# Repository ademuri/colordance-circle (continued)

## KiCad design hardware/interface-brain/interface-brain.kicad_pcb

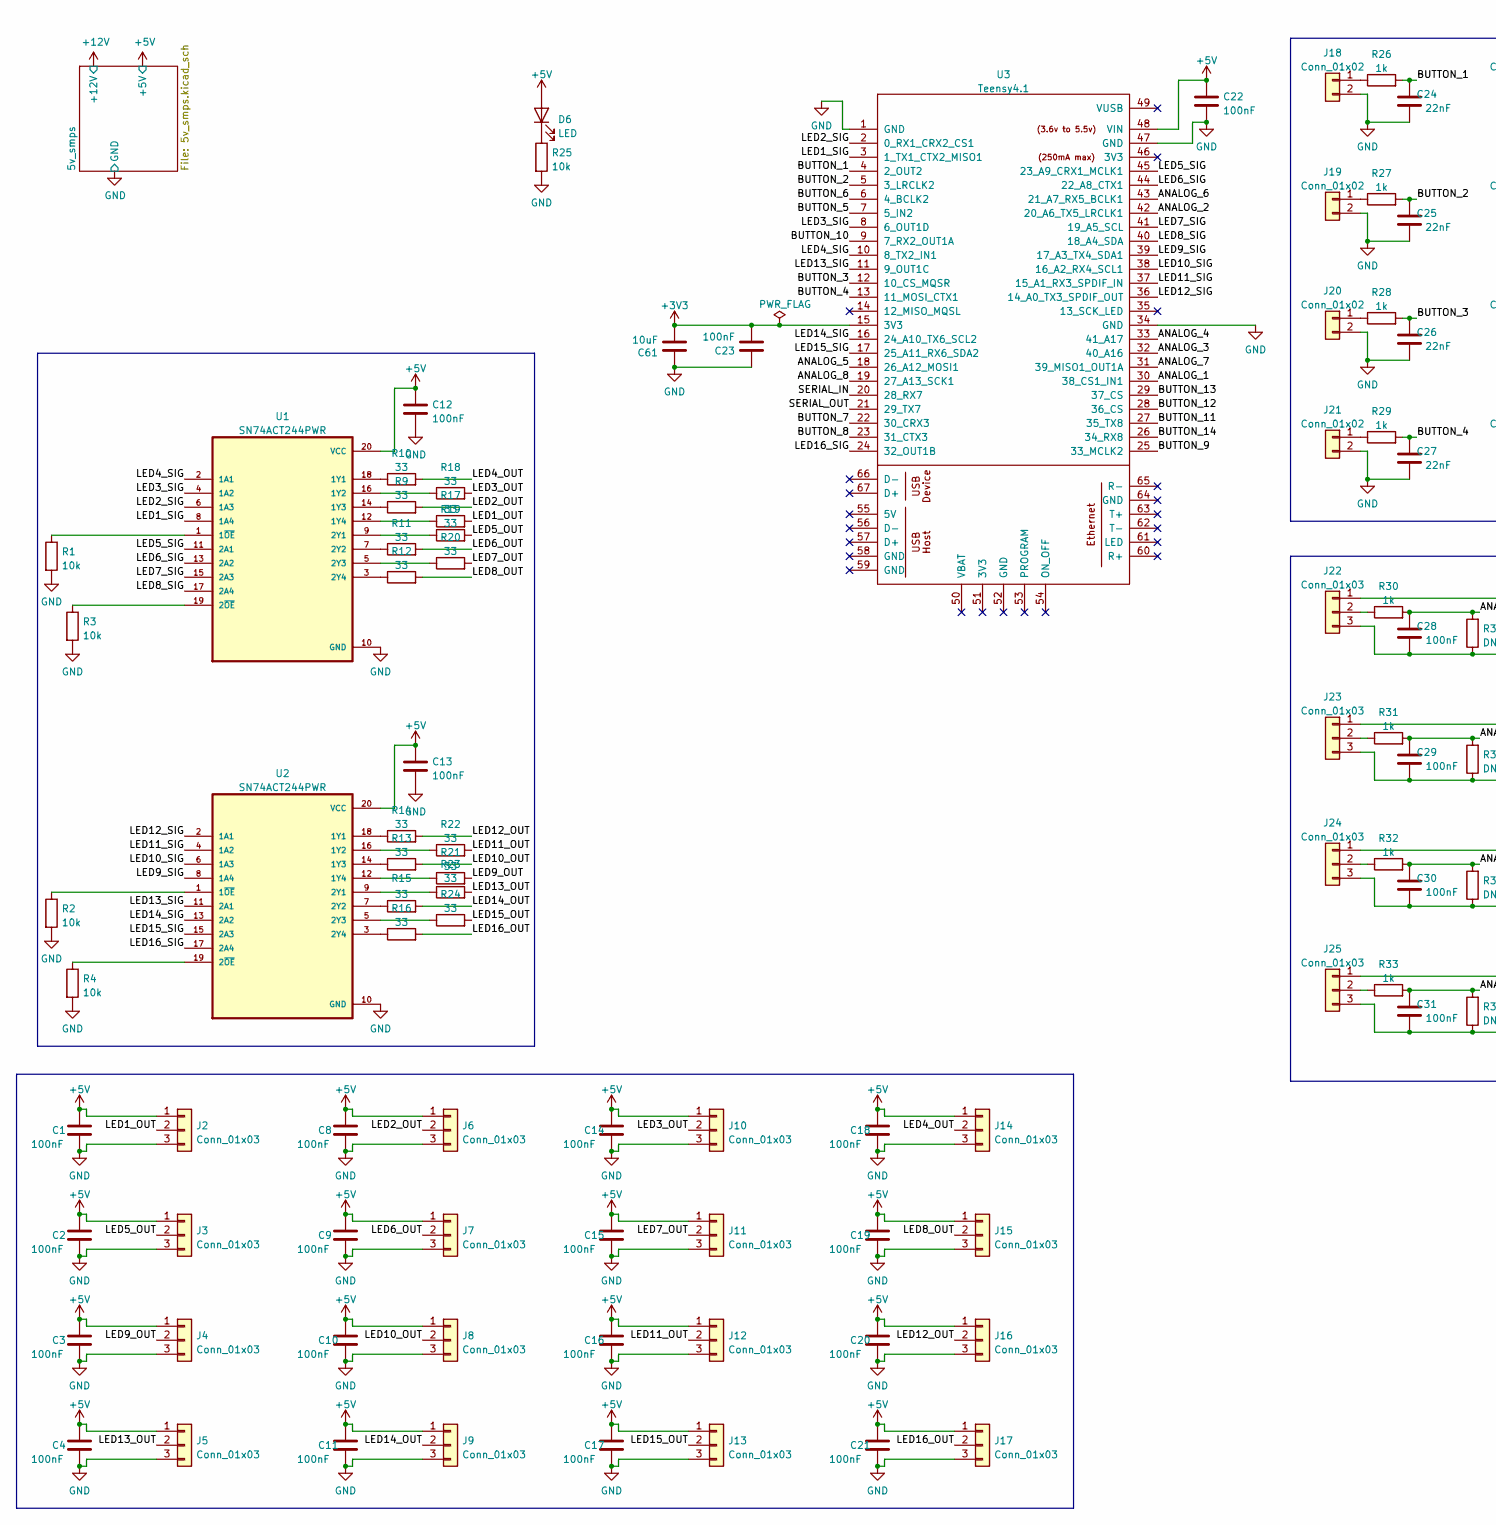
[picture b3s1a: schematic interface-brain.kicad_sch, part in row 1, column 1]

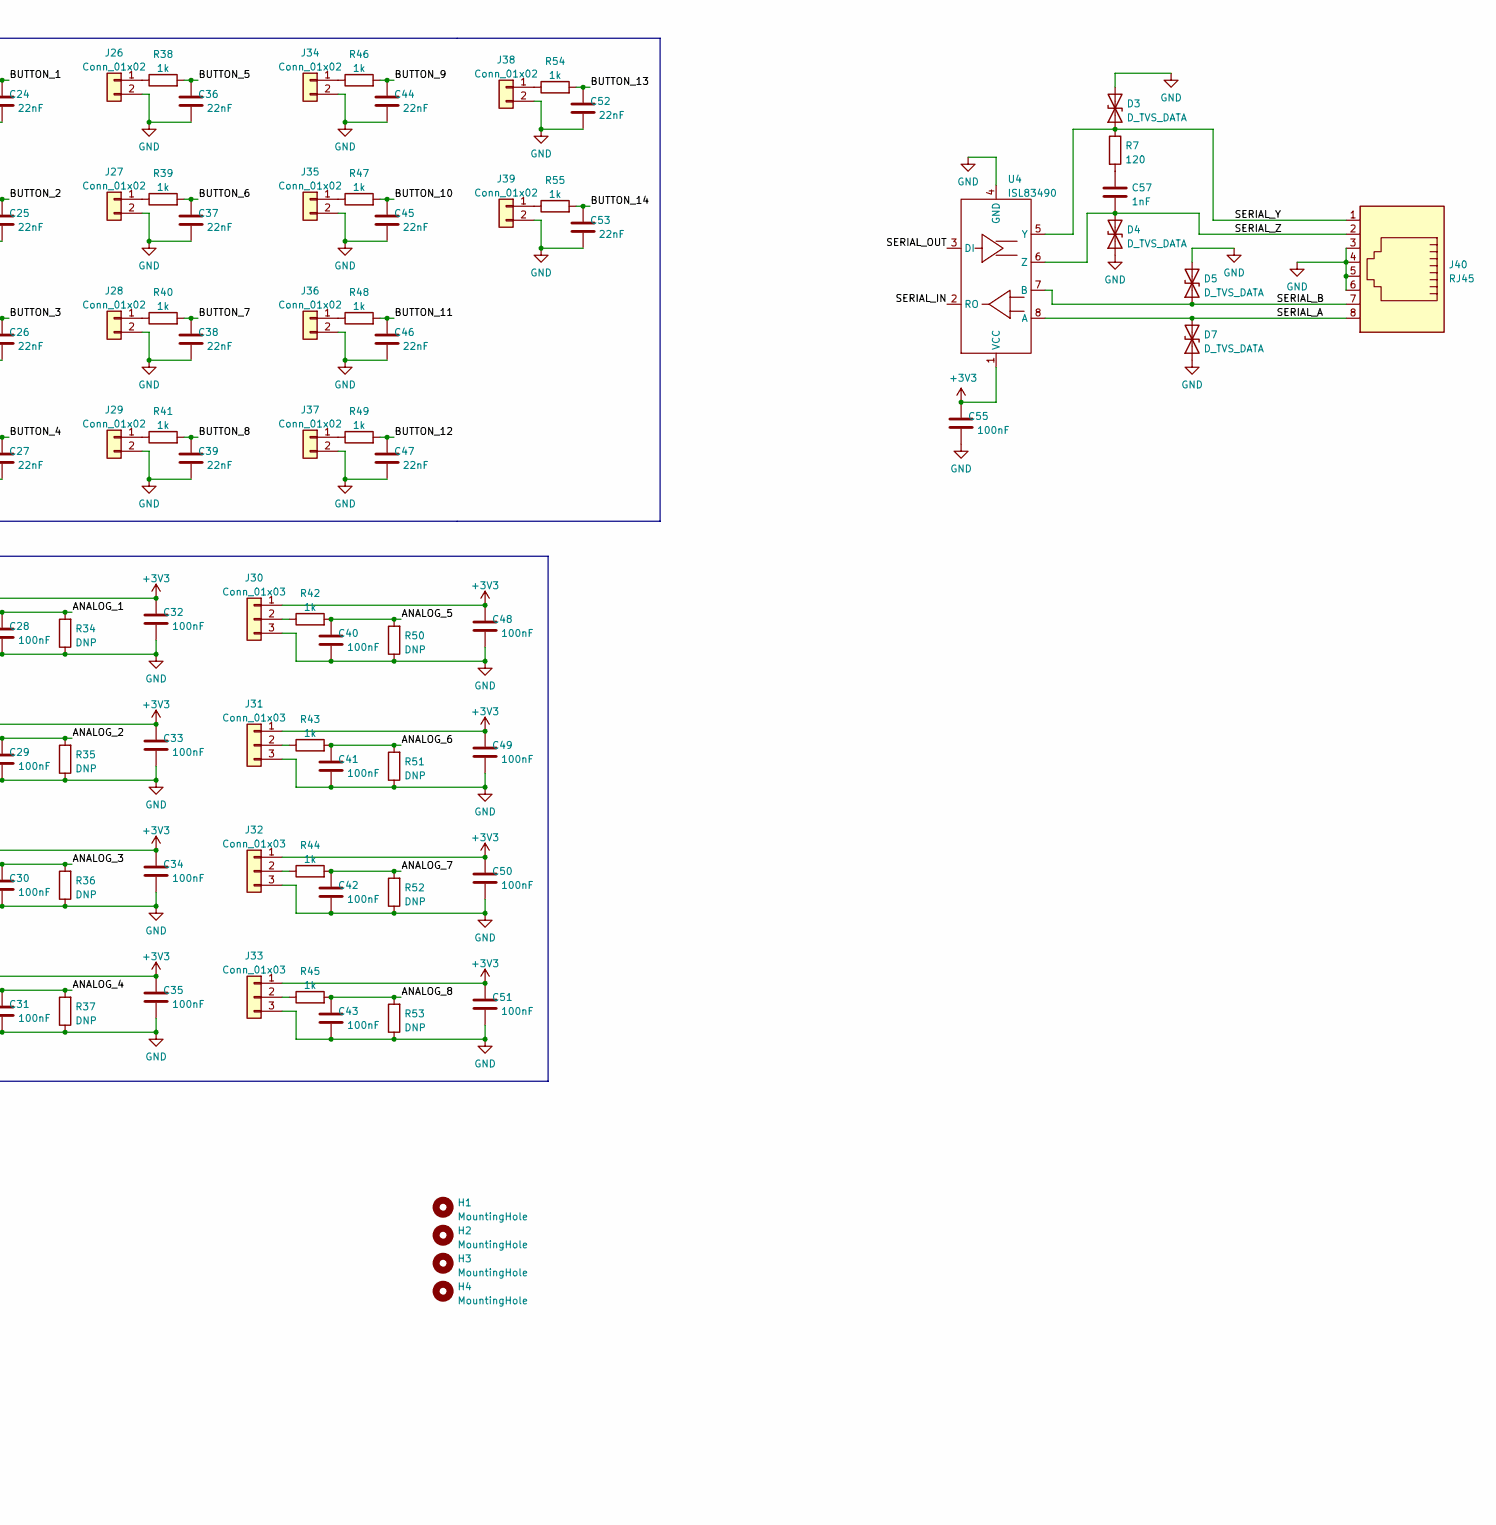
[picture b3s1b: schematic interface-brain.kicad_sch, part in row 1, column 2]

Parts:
C1, C2, C3, C4, C8, C9, C10, C11, C12, C13, C14, C15, C16, C17, C18, C19, C20, C21, C22, C23, C28, C29, C30, C31, C32, C33, C34, C35, C40, C41, C42, C43, C48, C49, C50, C51, C55: 100nF; C_0402_1005Metric; LCSC C307331
C24, C25, C26, C27, C36, C37, C38, C39, C44, C45, C46, C47, C52, C53: 22nF; C_0402_1005Metric; LCSC C1532
C57: 1nF; C_0402_1005Metric; LCSC C1523
C61: 10uF; C_0805_2012Metric; LCSC C15850
D3, D4, D5, D7: D_TVS_DATA; D_SMB; MPN SMBJ6.0CD-M3/H
D6: LED; LED_0603_1608Metric; LCSC C2286
H1, H2, H3, H4: MountingHole; MountingHole_3.2mm_M3
J2, J3, J4, J5, J6, J7, J8, J9, J10, J11, J12, J13, J14, J15, J16, J17, J22, J23, J24, J25, J30, J31, J32, J33: Conn_01x03; MiniPV_69167-X03XXX_1x03_P2.54mm_Polarized_Vertical; MPN 69167-103HLF
J18, J19, J20, J21, J26, J27, J28, J29, J34, J35, J36, J37, J38, J39: Conn_01x02; MiniPV_76384-X02XX_1x02_P2.54mm_Vertical; MPN 76384-302LF
J40: RJ45; RJ45_Amphenol_54602-x08_Horizontal; MPN 54601-908WPLF
R1, R2, R3, R4, R25: 10k; R_0603_1608Metric; LCSC C25804
R7: 120; R_0603_1608Metric; LCSC C22787
R9, R10, R11, R12, R13, R14, R15, R16, R17, R18, R19, R20, R21, R22, R23, R24: 33; R_0603_1608Metric; LCSC C23140
R26, R27, R28, R29, R30, R31, R32, R33, R38, R39, R40, R41, R42, R43, R44, R45, R46, R47, R48, R49, R54, R55: 1k; R_0603_1608Metric; LCSC C21190
R34, R35, R36, R37, R50, R51, R52, R53: DNP; R_0603_1608Metric
U1, U2: SN74ACT244PWR; TSSOP-20_4.4x6.5mm_P0.65mm; LCSC C6930
U3: Teensy4.1; Teensy41_stripped; MPN PPPC241LFBN-RC
U4: ISL83490; SOIC-8_3.9x4.9mm_P1.27mm; MPN ISL83490IBZ-T

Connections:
+3V3: C23.2, C32.1, C33.1, C34.1, C35.1, C48.1, C49.1, C50.1, C51.1, C55.1, C61.2, J22.1, J23.1, J24.1, J25.1, J30.1, J31.1, J32.1, J33.1, U3.15 (3V3), U4.1 (VCC)
+5V: C1.2, C2.2, C3.2, C4.2, C8.2, C9.2, C10.2, C11.2, C12.1, C13.1, C14.2, C15.2, C16.2, C17.2, C18.2, C19.2, C20.2, C21.2, C22.1, D6.2 (A), J2.1, J3.1, J4.1, J5.1, J6.1, J7.1, J8.1, J9.1, J10.1, J11.1, J12.1, J13.1, J14.1, J15.1, J16.1, J17.1, U1.20 (VCC), U2.20 (VCC), U3.48 (VIN); also elsewhere on the board
/ANALOG_1: C28.1, R30.2, R34.2, U3.30 (38_CS1_IN1)
/ANALOG_2: C29.1, R31.2, R35.2, U3.42 (20_A6_TX5_LRCLK1)
/ANALOG_3: C30.1, R32.2, R36.2, U3.32 (40_A16)
/ANALOG_4: C31.1, R33.2, R37.2, U3.33 (41_A17)
/ANALOG_5: C40.1, R42.2, R50.2, U3.18 (26_A12_MOSI1)
/ANALOG_6: C41.1, R43.2, R51.2, U3.43 (21_A7_RX5_BCLK1)
/ANALOG_7: C42.1, R44.2, R52.2, U3.31 (39_MISO1_OUT1A)
/ANALOG_8: C43.1, R45.2, R53.2, U3.19 (27_A13_SCK1)
/BUTTON_1: C24.1, R26.2, U3.4 (2_OUT2)
/BUTTON_2: C25.1, R27.2, U3.5 (3_LRCLK2)
/BUTTON_3: C26.1, R28.2, U3.12 (10_CS_MQSR)
/BUTTON_4: C27.1, R29.2, U3.13 (11_MOSI_CTX1)
/BUTTON_5: C36.1, R38.2, U3.7 (5_IN2)
/BUTTON_6: C37.1, R39.2, U3.6 (4_BCLK2)
/BUTTON_7: C38.1, R40.2, U3.22 (30_CRX3)
/BUTTON_8: C39.1, R41.2, U3.23 (31_CTX3)
/BUTTON_9: C44.1, R46.2, U3.25 (33_MCLK2)
/BUTTON_10: C45.1, R47.2, U3.9 (7_RX2_OUT1A)
/BUTTON_11: C46.1, R48.2, U3.27 (35_TX8)
/BUTTON_12: C47.1, R49.2, U3.28 (36_CS)
/BUTTON_13: C52.1, R54.2, U3.29 (37_CS)
/BUTTON_14: C53.1, R55.2, U3.26 (34_RX8)
/LED1_OUT: J2.2, R17.2
/LED1_SIG: U1.8 (1A4), U3.3 (1_TX1_CTX2_MISO1)
/LED2_OUT: J6.2, R9.2
/LED2_SIG: U1.6 (1A3), U3.2 (0_RX1_CRX2_CS1)
/LED3_OUT: J10.2, R18.2
/LED3_SIG: U1.4 (1A2), U3.8 (6_OUT1D)
/LED4_OUT: J14.2, R10.2
/LED4_SIG: U1.2 (1A1), U3.10 (8_TX2_IN1)
/LED5_OUT: J3.2, R19.2
/LED5_SIG: U1.11 (2A1), U3.45 (23_A9_CRX1_MCLK1)
/LED6_OUT: J7.2, R11.2
/LED6_SIG: U1.13 (2A2), U3.44 (22_A8_CTX1)
/LED7_OUT: J11.2, R20.2
/LED7_SIG: U1.15 (2A3), U3.41 (19_A5_SCL)
/LED8_OUT: J15.2, R12.2
/LED8_SIG: U1.17 (2A4), U3.40 (18_A4_SDA)
/LED9_OUT: J4.2, R21.2
/LED9_SIG: U2.8 (1A4), U3.39 (17_A3_TX4_SDA1)
/LED10_OUT: J8.2, R13.2
/LED10_SIG: U2.6 (1A3), U3.38 (16_A2_RX4_SCL1)
/LED11_OUT: J12.2, R22.2
/LED11_SIG: U2.4 (1A2), U3.37 (15_A1_RX3_SPDIF_IN)
/LED12_OUT: J16.2, R14.2
/LED12_SIG: U2.2 (1A1), U3.36 (14_A0_TX3_SPDIF_OUT)
/LED13_OUT: J5.2, R23.2
/LED13_SIG: U2.11 (2A1), U3.11 (9_OUT1C)
/LED14_OUT: J9.2, R15.2
/LED14_SIG: U2.13 (2A2), U3.16 (24_A10_TX6_SCL2)
/LED15_OUT: J13.2, R24.2
/LED15_SIG: U2.15 (2A3), U3.17 (25_A11_RX6_SDA2)
/LED16_OUT: J17.2, R16.2
/LED16_SIG: U2.17 (2A4), U3.24 (32_OUT1B)
/SERIAL_A: D7.2 (A2), J40.8, U4.8 (A)
/SERIAL_B: D5.1 (A1), J40.7, U4.7 (B)
/SERIAL_IN: U3.20 (28_RX7), U4.2 (RO)
/SERIAL_OUT: U3.21 (29_TX7), U4.3 (DI)
/SERIAL_Y: D3.1 (A1), J40.1, R7.1, U4.5 (Y)
/SERIAL_Z: C57.2, D4.2 (A2), J40.2, U4.6 (Z)
GND: C1.1, C2.1, C3.1, C4.1, C8.1, C9.1, C10.1, C11.1, C12.2, C13.2, C14.1, C15.1, C16.1, C17.1, C18.1, C19.1, C20.1, C21.1, C22.2, C23.1, C24.2, C25.2, C26.2, C27.2, C28.2, C29.2, C30.2, C31.2, C32.2, C33.2, C34.2, C35.2, C36.2, C37.2, C38.2, C39.2, C40.2, C41.2, C42.2, C43.2, C44.2, C45.2, C46.2, C47.2, C48.2, C49.2, C50.2, C51.2, C52.2, C53.2, C55.2, C61.1, D3.2 (A2), D4.1 (A1), D5.2 (A2), D7.1 (A1), J2.3, J3.3, J4.3, J5.3, J6.3, J7.3, J8.3, J9.3, J10.3, J11.3, J12.3, J13.3, J14.3, J15.3, J16.3, J17.3, J18.2, J19.2, J20.2, J21.2, J22.3, J23.3, J24.3, J25.3, J26.2, J27.2, J28.2, J29.2, J30.3, J31.3, J32.3, J33.3, J34.2, J35.2, J36.2, J37.2, J38.2, J39.2, J40.3, J40.4, J40.5, J40.6, R1.2, R2.2, R3.2, R4.2, R25.2, R34.1, R35.1, R36.1, R37.1, R50.1, R51.1, R52.1, R53.1, U1.10 (GND), U2.10 (GND), U3.1 (GND), U3.34 (GND), U3.47 (GND), U4.4 (GND); also elsewhere on the board
unnamed: C57.1, R7.2
unnamed: D6.1 (K), R25.1
unnamed: J18.1, R26.1
unnamed: J19.1, R27.1
unnamed: J20.1, R28.1
unnamed: J21.1, R29.1
unnamed: J22.2, R30.1
unnamed: J23.2, R31.1
unnamed: J24.2, R32.1
unnamed: J25.2, R33.1
unnamed: J26.1, R38.1
unnamed: J27.1, R39.1
unnamed: J28.1, R40.1
unnamed: J29.1, R41.1
unnamed: J30.2, R42.1
unnamed: J31.2, R43.1
unnamed: J32.2, R44.1
unnamed: J33.2, R45.1
unnamed: J34.1, R46.1
unnamed: J35.1, R47.1
unnamed: J36.1, R48.1
unnamed: J37.1, R49.1
unnamed: J38.1, R54.1
unnamed: J39.1, R55.1
unnamed: R1.1, U1.1 (1~OE)
unnamed: R2.1, U2.1 (1~OE)
unnamed: R3.1, U1.19 (2~OE)
unnamed: R4.1, U2.19 (2~OE)
unnamed: R9.1, U1.14 (1Y3)
unnamed: R10.1, U1.18 (1Y1)
unnamed: R11.1, U1.7 (2Y2)
unnamed: R12.1, U1.3 (2Y4)
unnamed: R13.1, U2.14 (1Y3)
unnamed: R14.1, U2.18 (1Y1)
unnamed: R15.1, U2.7 (2Y2)
unnamed: R16.1, U2.3 (2Y4)
unnamed: R17.1, U1.12 (1Y4)
unnamed: R18.1, U1.16 (1Y2)
unnamed: R19.1, U1.9 (2Y1)
unnamed: R20.1, U1.5 (2Y3)
unnamed: R21.1, U2.12 (1Y4)
unnamed: R22.1, U2.16 (1Y2)
unnamed: R23.1, U2.9 (2Y1)
unnamed: R24.1, U2.5 (2Y3)

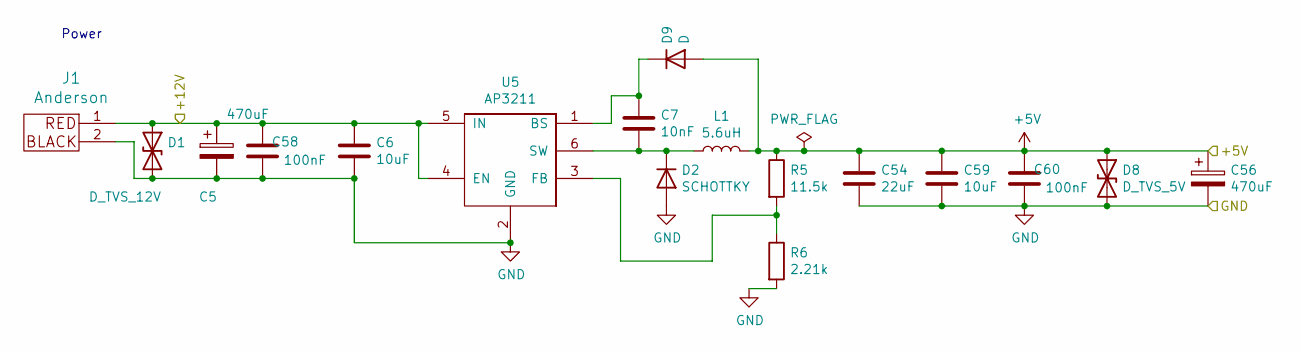
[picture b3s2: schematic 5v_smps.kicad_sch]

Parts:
C5, C56: 470uF; CP_Radial_D10.0mm_P5.00mm; MPN ESC477M035AH4EA
C6, C59: 10uF; C_0805_2012Metric; LCSC C15850
C7: 10nF; C_0402_1005Metric; LCSC C15195
C54: 22uF; C_1206_3216Metric; LCSC C12891
C58, C60: 100nF; C_0402_1005Metric; LCSC C307331
D1: D_TVS_12V; D_SMB; MPN SMBJ13CA
D2: SCHOTTKY; D_SMA; LCSC C8678
D8: D_TVS_5V; D_SMB; MPN SMBJ6.0CD-M3/H
D9: D; D_SMA; LCSC C8678
J1: Anderson; Anderson_1336G1_right_angle_bottom_two
L1: 5.6uH; L_Taiyo-Yuden_NR-60xx; MPN NR6028T6R0M
R5: 11.5k; R_0603_1608Metric; MPN RMCF0603FT11K5
R6: 2.21k; R_0603_1608Metric; MPN RC1608F2211CS
U5: AP3211; SOT-23-6; MPN AP3211KTR-G1

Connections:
+5V: C54.1, C56.1, C59.1, C60.1, D8.1 (A1), D9.2 (A), L1.2, R5.1; also elsewhere on the board
+12V: C5.1, C6.1, C58.1, D1.1 (A1), J1.1, U5.4 (EN), U5.5 (IN)
GND: C5.2, C6.2, C54.2, C56.2, C58.2, C59.2, C60.2, D1.2 (A2), D2.2 (A), D8.2 (A2), J1.2, R6.2, U5.2 (GND); also elsewhere on the board
unnamed: C7.1, D9.1 (K), U5.1 (BS)
unnamed: C7.2, D2.1 (K), L1.1, U5.6 (SW)
unnamed: R5.2, R6.1, U5.3 (FB)

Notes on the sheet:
Power

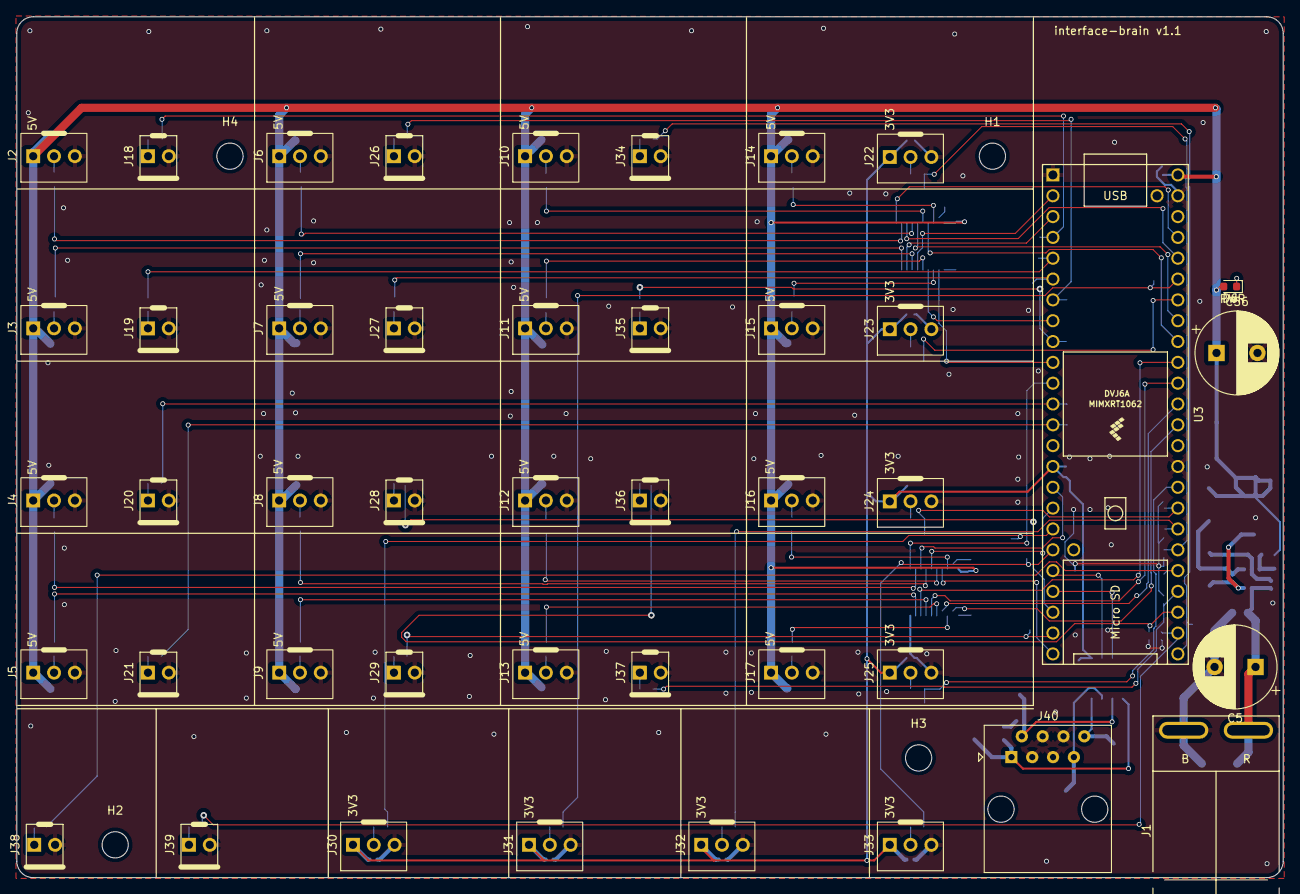
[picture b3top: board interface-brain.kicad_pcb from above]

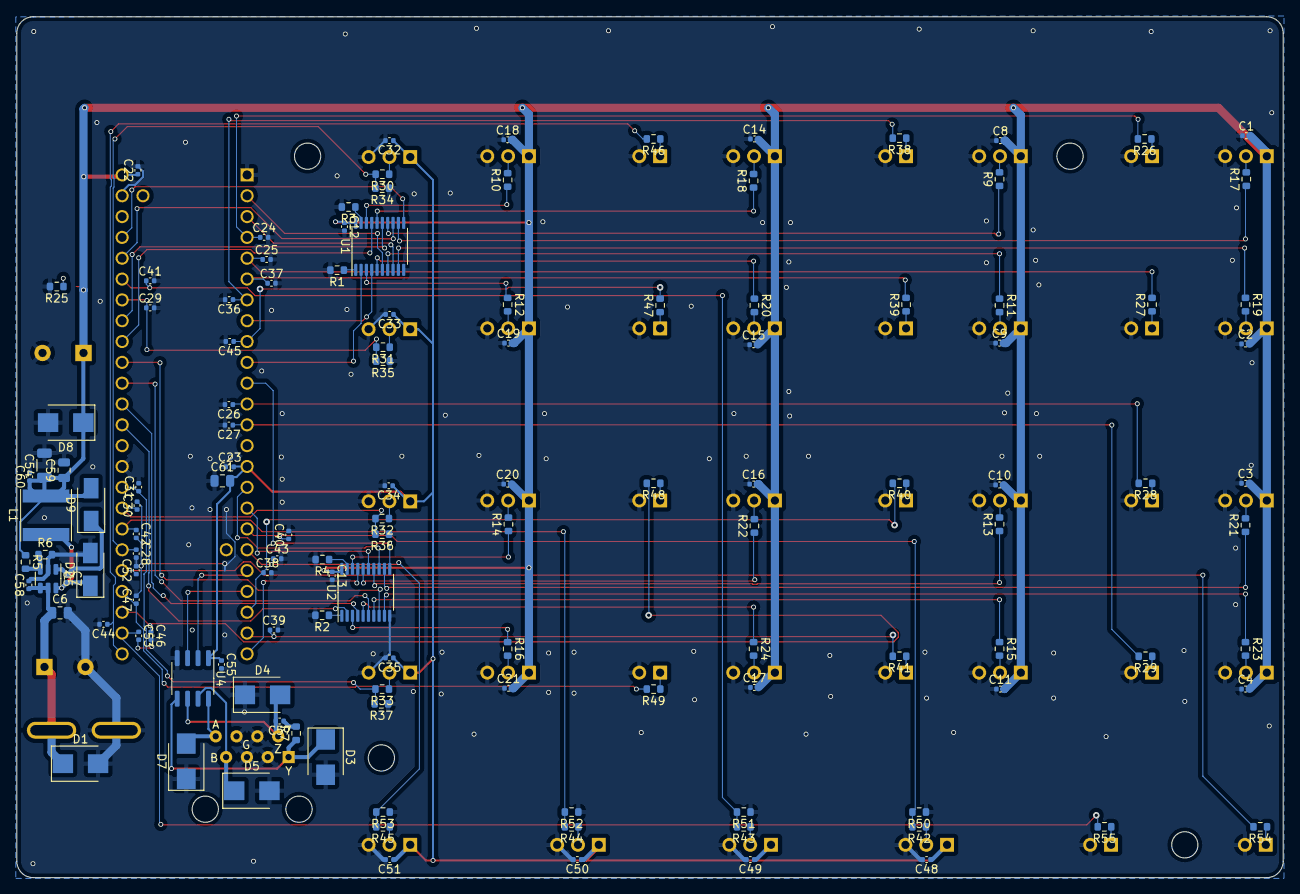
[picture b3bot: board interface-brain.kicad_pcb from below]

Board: 2 copper layers, 154.5 x 105.0 mm, 174 parts (126 on the bottom side), 111 nets.

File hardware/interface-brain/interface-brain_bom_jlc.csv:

"Comment","Designator","Footprint","LCSC Part #"
"100nF","C1,C2,C3,C4,C8,C9,C10,C11,C12,C13,C14,C15,C16,C17,C18,C19,C20,C21,C22,C23,C28,C29,C30,C31,C32,C33,C34,C35,C40,C41,C42,C43,C48,C49,C50,C51,C55,C58,C60","C_0402_1005Metric","C307331"
"10nF","C7","C_0402_1005Metric","C15195"
"22nF","C24,C25,C26,C27,C36,C37,C38,C39,C44,C45,C46,C47,C52,C53","C_0402_1005Metric","C1532"
"22uF","C54","C_1206_3216Metric","C12891"
"1nF","C57","C_0402_1005Metric","C1523"
"10uF","C61,C6,C59","C_0805_2012Metric","C15850"
"SCHOTTKY","D2","D_SMA","C8678"
"LED","D6","LED_0603_1608Metric","C2286"
"D","D9","D_SMA","C8678"
"10k","R1,R2,R3,R4,R25","R_0603_1608Metric","C25804"
"120","R7","R_0603_1608Metric","C22787"
"33","R9,R10,R11,R12,R13,R14,R15,R16,R17,R18,R19,R20,R21,R22,R23,R24","R_0603_1608Metric","C23140"
"1k","R26,R27,R28,R29,R30,R31,R32,R33,R38,R39,R40,R41,R42,R43,R44,R45,R46,R47,R48,R49,R54,R55","R_0603_1608Metric","C21190"
"SN74ACT244PWR","U1,U2","TSSOP-20_4.4x6.5mm_P0.65mm","C6930"

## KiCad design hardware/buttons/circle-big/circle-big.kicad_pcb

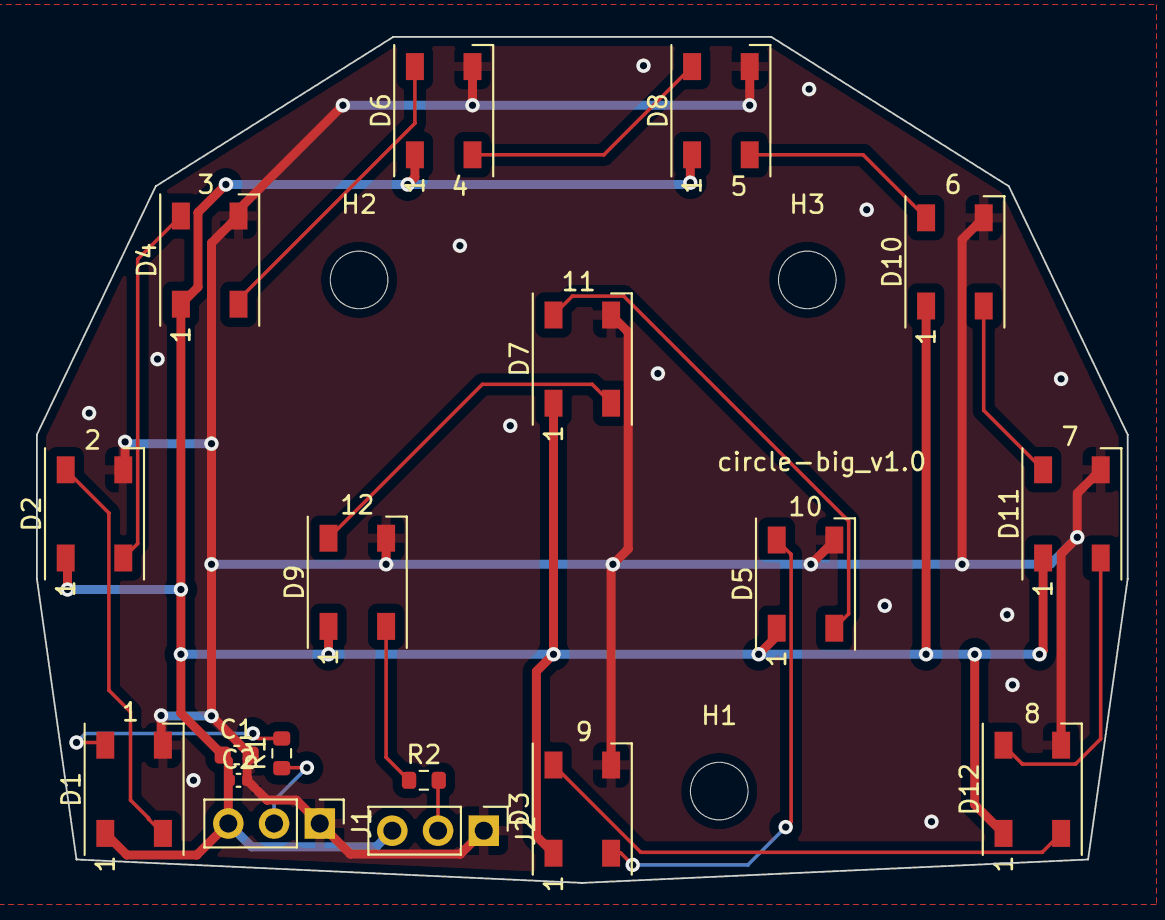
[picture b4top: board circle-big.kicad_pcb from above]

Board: 2 copper layers, 60.6 x 47.0 mm, 21 parts (0 on the bottom side), 17 nets.

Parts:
C1: 10uF; C_0603_1608Metric
C2: 100nF; C_0402_1005Metric
D1, D2, D3, D4, D5, D6, D7, D8, D9, D10, D11, D12: WS2812B; LED_WS2812B_PLCC4_5.0x5.0mm_P3.2mm
H1, H2, H3: MountingHole; MountingHole_3.2mm_M3
J1, J2: Conn_01x03; PinHeader_1x03_P2.54mm_Vertical
R1, R2: 33; R_0603_1608Metric

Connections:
/SIG_IN: J1.2, R1.1
/SIG_OUT: J2.2, R2.2
GND: C1.2, C2.2, D1.3 (VSS), D2.3 (VSS), D3.3 (VSS), D4.3 (VSS), D5.3 (VSS), D6.3 (VSS), D7.3 (VSS), D8.3 (VSS), D9.3 (VSS), D10.3 (VSS), D11.3 (VSS), D12.3 (VSS), J1.1, J2.1
unnamed: D1.2 (DOUT), D2.4 (DIN)
unnamed: D1.4 (DIN), R1.2
unnamed: D2.2 (DOUT), D4.4 (DIN)
unnamed: D3.2 (DOUT), D5.4 (DIN)
unnamed: D4.2 (DOUT), D6.4 (DIN)
unnamed: D5.2 (DOUT), D7.4 (DIN)
unnamed: D6.2 (DOUT), D8.4 (DIN)
unnamed: D7.2 (DOUT), D9.4 (DIN)
unnamed: D9.2 (DOUT), R2.1
unnamed: D10.2 (DOUT), D11.4 (DIN)
unnamed: D8.2 (DOUT), D10.4 (DIN)
unnamed: D11.2 (DOUT), D12.4 (DIN)
unnamed: D3.4 (DIN), D12.2 (DOUT)
VCC: C1.1, C2.1, D1.1 (VDD), D2.1 (VDD), D3.1 (VDD), D4.1 (VDD), D5.1 (VDD), D6.1 (VDD), D7.1 (VDD), D8.1 (VDD), D9.1 (VDD), D10.1 (VDD), D11.1 (VDD), D12.1 (VDD), J1.3, J2.3

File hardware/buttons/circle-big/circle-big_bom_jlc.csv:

"Comment","Designator","Footprint","LCSC Part #"
"10uF","C1","C_0603_1608Metric","C96446"
"100nF","C2","C_0402_1005Metric","C307331"
"WS2812B","D1,D2,D3,D4,D5,D6,D7,D8,D9,D10,D11,D12","LED_WS2812B_PLCC4_5.0x5.0mm_P3.2mm","C2761796"
"33","R1,R2","R_0603_1608Metric","C23140"

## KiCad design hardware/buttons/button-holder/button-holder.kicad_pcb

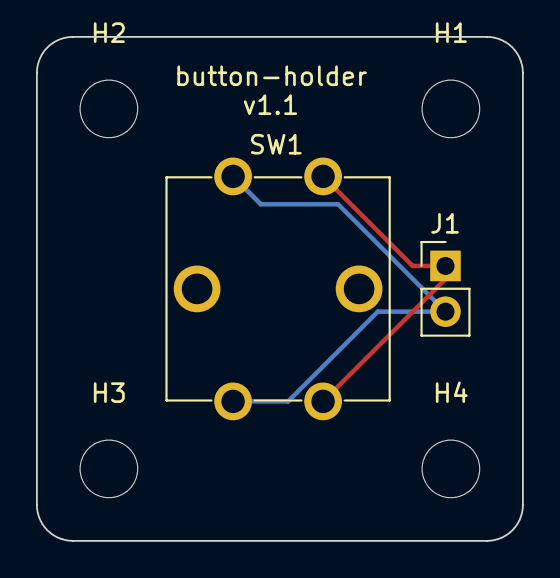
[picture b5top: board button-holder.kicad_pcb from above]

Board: 2 copper layers, 27.0 x 28.0 mm, 6 parts (0 on the bottom side), 2 nets.

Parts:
H1, H2, H3, H4: MountingHole; MountingHole_3.2mm_M3
J1: Conn_01x02; PinHeader_1x02_P2.54mm_Vertical
SW1: SW_SPST; SW_Tactile_SPST_TL6300

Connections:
unnamed: J1.1, SW1.1 (A)
unnamed: J1.2, SW1.2 (B)

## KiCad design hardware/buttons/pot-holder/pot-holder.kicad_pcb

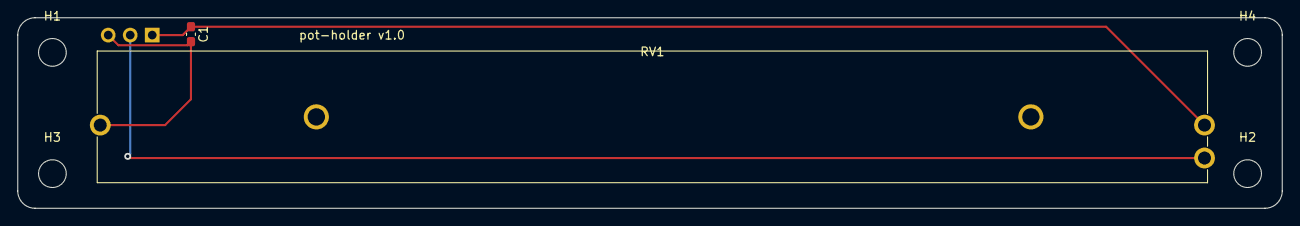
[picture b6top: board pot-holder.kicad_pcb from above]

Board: 2 copper layers, 146.0 x 22.0 mm, 7 parts (1 on the bottom side), 3 nets.

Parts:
C1: C; C_0603_1608Metric_Pad1.08x0.95mm_HandSolder
H1, H2, H3, H4: MountingHole; MountingHole_3.2mm_M3
J1: Conn_01x03; PinHeader_1x03_P2.54mm_Vertical
RV1: R_Potentiometer; Potentiometer_Bourns_PTB01X3_Single_Slide

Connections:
unnamed: C1.1, J1.1, RV1.1
unnamed: C1.2, J1.3, RV1.3
unnamed: J1.2, RV1.2

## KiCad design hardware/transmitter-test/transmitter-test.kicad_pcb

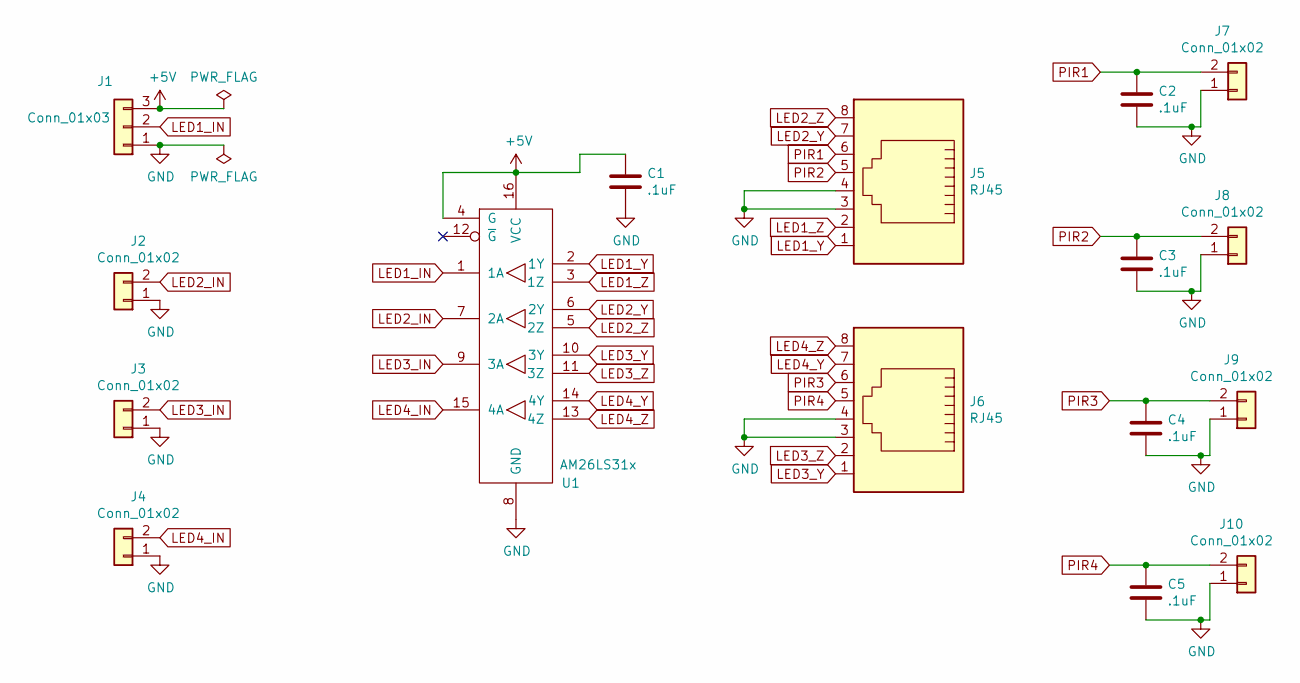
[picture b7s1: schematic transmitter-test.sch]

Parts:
C1, C2, C3, C4, C5: .1uF; C_0603_1608Metric_Pad1.05x0.95mm_HandSolder
J1: Conn_01x03; PinHeader_1x03_P2.54mm_Vertical
J2, J3, J4, J7, J8, J9, J10: Conn_01x02; PinHeader_1x02_P2.54mm_Vertical
J5, J6: RJ45; RJ45_Amphenol_54602-x08_Horizontal
U1: AM26LS31x; SOIC-16_3.9x9.9mm_P1.27mm

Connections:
+5V: C1.1, J1.3, U1.4 (G), U1.16 (VCC)
GND: C1.2, C2.2, C3.2, C4.2, C5.2, J1.1, J2.1, J3.1, J4.1, J5.3, J5.4, J6.3, J6.4, J7.1, J8.1, J9.1, J10.1, U1.8 (GND)
LED1_IN: J1.2, U1.1 (1A)
LED1_Y: J5.1, U1.2 (1Y)
LED1_Z: J5.2, U1.3 (1Z)
LED2_IN: J2.2, U1.7 (2A)
LED2_Y: J5.7, U1.6 (2Y)
LED2_Z: J5.8, U1.5 (2Z)
LED3_IN: J3.2, U1.9 (3A)
LED3_Y: J6.1, U1.10 (3Y)
LED3_Z: J6.2, U1.11 (3Z)
LED4_IN: J4.2, U1.15 (4A)
LED4_Y: J6.7, U1.14 (4Y)
LED4_Z: J6.8, U1.13 (4Z)
PIR1: C2.1, J5.6, J7.2
PIR2: C3.1, J5.5, J8.2
PIR3: C4.1, J6.6, J9.2
PIR4: C5.1, J6.5, J10.2

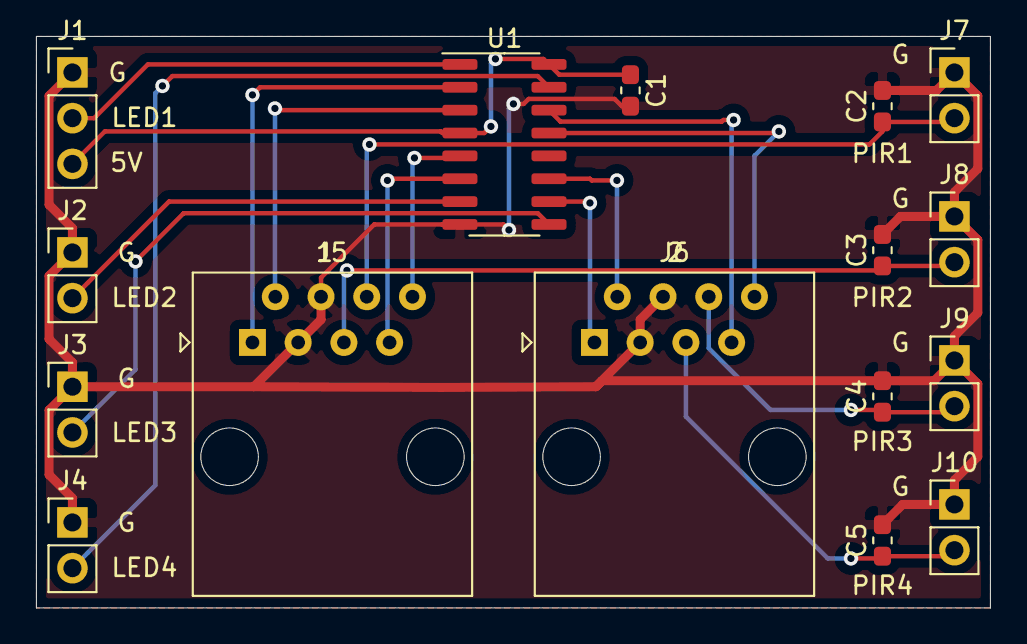
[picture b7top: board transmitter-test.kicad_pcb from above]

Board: 2 copper layers, 53.0 x 31.8 mm, 16 parts (0 on the bottom side), 18 nets.

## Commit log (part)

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2019-11-24 Add an empty README
2019-11-24 Create a pole class
2019-11-24 Make Boost optional
2019-11-24 Format all code
2019-11-24 Add escape key to exit
2019-11-27 Add symlink for YCM file
2019-11-27 Add a light controller.
    Implement it in Ogre.
2019-11-27 Add an effect class, and a basic color cycle effect.
2019-11-27 Add hook to automatically format files on commit
2019-11-27 Add SetGridLight overload for HSV
2019-11-28 Add tests for the effects.
    This tests stability (by running for 12 simulated hours) and power
    consumption.
2019-11-28 Add a sketch (no-op) and Makefile for Arduino.
2019-11-28 Fail power test if average or max power is too high
2019-12-01 Add runtime option to use real or fake millis().
    This fixes the simulator.
2019-12-05 Add some modes to the color cycle effect.
2019-12-05 Add a mini circle effect.
2019-12-08 Add more effects to Arduino runner
2019-12-08 Add modes to RotateThree.
    Adds (left-to-right, up-to-down) x (same direction, changing
    directions).
2019-12-08 Add a CrossEffect.
2019-12-08 Allow changing number of poles for rotate three
2019-12-08 Add an option to disable building the simulator.
2019-12-11 Fix typo in port in makefile
2019-12-11 Add constants for number of poles and grid size
2019-12-11 Enable temporal dithering for FastLED
2019-12-14 Add sin-fade effects to ColorCycle
2019-12-14 Add a ClearGridLights method to Pole.
2019-12-14 Use the param controller in ColorCycleEffect.
2019-12-14 Add target to arduino Makefile to automatically download arduino-cli.
2019-12-14 Ignore remaining FakeFastLED warnings.
2019-12-14 Switch ParamController to using an enum for params.
2020-01-02 Clean up processing controller
    Extract slider into a reusable class.
2020-01-02 Add a readme for the processing controller
2020-01-02 Add documentation for param identifier
2020-01-04 Add button to controller
2020-01-07 Add license
2020-01-15 WIP fix arudino compile
2020-01-15 WIP fix build
2020-01-17 Move third-party code to `third_party`.
2020-02-23 Add script to run tests
2020-02-23 Add script to build Arduino code
2020-03-04 Add transmitter test board v1.0
2020-03-08 Fix arduino-cli config to work with latest version (v0.9.0)
2020-03-08 Added FlashEffect
2021-03-20 git subrepo clone https://github.com/ademuri/cmake-fetch-content.git
    subrepo:
    subdir: "cmake-fetch-content"
    merged: "b45b0b5"
    upstream:
    origin: "https://github.com/ademuri/cmake-fetch-content.git"
    branch: "master"
2021-03-20 Migrate to PlatformIO.
    This uses Platformio to build Arduino code, instead of a terrible
    hacked-together Makefile.
2021-04-02 Update controlled effects. In progress!
2021-04-03 Add basic web server code
2021-04-22 Update pole node to v1.1
    This adds lots of TVS diode, more decoupling, bulk caps on 5v and 12v
    lines. Also adds pass-through Anderson connector.
2021-05-20 More work on colordance-brain
    - Define hierarchical sheet for RS422 output
    - Update power supply
2021-05-20 Colordance brain v1.0
2021-06-12 Add PCB spacer
2021-08-25 Controlled effect update and start of Demo code. IN PROGRESS
2021-09-02 Update Sam's code to PlatformIO
2021-09-02 Prepare for multiple platforms
2021-09-03 Add support for Teensy platform (untested)
2021-09-08 Fix teensy bug
2021-09-09 Ignore vscode
2021-09-09 Update pixel color order
2021-09-09 Fix first 4 LED port numbers
2021-09-09 Seed random using Entropy library
2022-04-15 Random hardware changes
2022-04-24 Add schematic for interface-brain
2022-04-25 Assign footprints and part numbers
2022-04-27 Continue interface brain layout
2022-04-28 Interface brain layout almost done
2022-04-29 Add interface LED layout
2022-04-30 Add square button
2022-04-30 Add heart button
2022-04-30 Add mounting holes
2022-04-30 Add big and small buttons
2022-05-09 Add STEP and STLs for interface PCBs
2022-05-10 Add numerical mapping of LED strips.
2022-05-10 Add debug settings for lights and controls
2022-05-10 Add analog input reading to interface
2022-05-11 Add CI config
2022-05-11 Fix tests
2022-05-11 Remove outdated build section from readme
2022-05-13 Add SpiParamController
2022-05-16 Continue fixing debug controls
2022-05-29 Refactor and start adding effects
2022-06-06 Fix case in include paths
2022-06-06 Inline trivial function, remove unnecessary user-defined default constructor
2022-06-06 Start refactoring
2022-06-07 better version printer
2022-06-07 Add 3D model for pot holder
2022-06-07 Turn on C++17 mode for PlatformIO
2022-06-07 Use values instead of pointers
2022-06-07 Use values instead of pointers for controlPoles
2022-06-07 Use a `std::unique_ptr` instead of raw `new` in `EffectsTest.cpp`
2022-06-07 Avoid unnecessary copies of `std::vector`
2022-06-08 Use `#pragma once` instead of macro guards
2022-06-08 Get Sliders, BackAndForth, and SideToSide working
2022-06-08 Use `unique_ptr` to manage lifetime in `Sliders`
2022-06-09 Functioning but incomplete demo.
2022-06-10 WIP port serial stuff
2022-06-10 Add serial param controller
2022-06-10 Remove serial pins from analog inputs for interface
2022-06-15 Fix pole-node port mappings
2022-06-18 Add gitignore for KiCAD temp files
2022-06-19 Run clang-format and add script for it
2022-06-19 Fix compile errors in tests
2022-06-19 Fix PIO compiler warnings
2022-06-19 Fix rfboard build
2022-06-19 Update effect integration test.
    - Cycle through the pole-effects
    - Add calculation for max pole power
    - Migrate from unique_ptr to raw pointers, since that more closely
    matches how this works on device
2022-06-19 Remove -Wno-register flag from pio
    It's not needed, and it causes compiler warnings, because it's only
    valid for C++, and pio applies to it C as well as C++.
2022-06-20 Convert colordance-brain to KiCAD 6
2022-06-20 Move power supply to subsheet
2022-06-24 interface-brain v1.1:
    - Switch to serial-over-RS422 for comms with colordance-brain
    - Add 12v supply + 5V SMPS
2022-07-02 Enable ASAN for tests
2022-07-04 Reduce scope of variable
2022-07-04 Reduce code duplication in `FastLedLightController`
2022-07-04 Reduce code duplication in `SimulatorLightController` and `TeensyLightController`
2022-07-04 Use a common `std::array` typedef instead of `std::vector`
2022-07-04 Remove unused member variables
2022-07-04 Do not use const data members. Do not use all caps for variables -- that is macro territory.
2022-07-04 More consistently use C++17 instead of sometimes C++11
2022-07-04 Declare some variables `const`
2022-07-04 Remove unused include
2022-07-04 Construct light controllers directly instead of allocating them on the heap
2022-07-04 Mark an overriding function `override`
2022-07-04 Simplify constructors for various implementations of `ParamController`
2022-07-04 Some versions of compilers we use do not support `inline` variables
2022-07-04 Include what you use
2022-07-04 Add dependency for interface
2022-07-04 Update README with build instructions
2022-07-06 Revert copy-paste error in Simulator
2022-07-06 Re-add CI config
2022-07-06 Add EasyTransfer dep to Teensy
2022-07-06 Add Wire lib dep to interface
2022-07-06 Move running the effect and param controller into a wrapper class.
    I'm going to add logic to do power management. This will show a dim
    ("attractor") pattern when no one is around. This logic will live in
    Runner, so that we can test it.
2022-07-06 Update simulator to display the LEDs directly.
    This migrates from using Ogre to SDL2.
2022-07-09 Add environment controller
2022-07-10 Switch to low-power mode when the battery voltage is low
2022-07-10 Fix rfboard env
    This adds a fake EnvironmenController.
2022-07-11 Ad hysteresis to battery voltage detection
2022-07-11 Rename DummyParamController -> FakeParamController
2022-07-11 Fix order dependence in RunnerTest
2022-07-17 Use a ParamController reference instead of pointer
2022-07-17 Move params as a member of ParamController
2022-07-17 Add change detection to param controllers
2022-07-17 Add an idle effect
2022-07-17 Update the idle effect
    This applies a sin wave to the brightnesses, to make it more visible
    from a distance, and reduce power consumption.
2022-07-17 Add pole lights
2022-07-17 Make pole lights smaller
2022-07-17 Make Runner order more consistent
2022-07-18 Make GetRawParam/GetScaledParam const
2022-07-18 Make some environment controller methods const
2022-07-18 Add a basic logger class
2022-07-18 Update teensy logger to check up to 9,999 log file names
2022-07-18 Log some params and environment values
2022-07-19 Fix logger test
2022-07-19 Update CI to build CMake tests in release mode.
    This speeds up the tests significantly. They still include debug
    symbols.
2022-07-22 Fix lag in simulator
2022-07-25 Add pole lights
    Add pole lights to all the effects.
    In the low poewr mode only the lowest LEDs on the pole display anything.
    Also added tests.
2022-07-25 Update html bom
2022-07-28 colordance-brain hardware v1.2:
    - Fix interface RJ45 port orientation
    - Add a third local PIR port
    - Fix interface to use a serial port, not a CAN port
    - Add a 470uF cap for the 3v3 rail
2022-07-31 Remove commented-out test code from teensy code
2022-08-02 Add a sketch for using the Teensy-based boards with the scale model.
2022-08-02 Fix LED output corruption isses
    Some LEDs were not being updated/written to. This is due to some
    interaction between receiving serial data and the Teensy FastLED
    library. The teensy serial ports use interrupts and a 4-byte buffer, and
    FastLED uses DMA with interrupts. This change fixes the issue by
    enforcing timing in the brain and interface code. It has a strict
    sequence, where the brain will receive the serial data at a specific
2022-08-03 General code review fixes
2022-08-03 Default battery to full in fake environment controller.
    This fixes the model going into low-power mode when using the firefly board.
2022-08-03 Update logging to flush the cache periodically.
2022-08-07 Clamp the LED channel brightness to a min of 10.
    The light panel LEDs do not light up reliably below this level - some
    LEDs light, and some do not. Removing this dead band will make the LED
    behavior more consistent.
2022-08-07 Add a rule for CMake to generate test coverage using gcov
2022-08-07 Add test covreage for the shift and beat buttons
2022-08-09 Code review fixes
2022-08-09 Code review fixes & lower power fixes
2022-08-14 Update shift timing and effects. Sticky broken.
2022-08-15 Add button LED interface
2022-08-15 Send runner state to interface
    Also move ControlsIn parsing into ParamController.
2022-08-15 Only build coverage if requested
2022-08-17 Fix test build
2022-08-18 Update interface buttons constants.
2022-08-22 Sort of fix interface.
2022-08-22 Interface changes
2022-08-30 SAFE
2023-05-29 WIP debugging changes
2023-05-29 Update colordance-brain PCB files to KiCAD 7
2023-05-29 Blink the interface LED to show it's alive
2023-05-29 Update colordance-brain to 1.3: JLC assembly (completed)
2023-05-29 Fix teensy light controller pins
2023-05-29 Debugging changes
2023-05-29 Fix pole-node v1.3 footprint for XL1509 SMPS
2023-05-29 Teensy cleanup
2023-05-29 Limit max LED refresh rate for interface
2023-05-29 Fix test build
    Tests are failing.
2023-05-29 Fix bug where MovingPoles wrote to an invalid button index.
2023-05-29 Fix test memory bug
2023-05-29 Update dependent actions to v3
2023-05-29 Disable rfboard build target.
    It fails to build because the program size is too large. We're not using
    the rfboard anymore, anyway.
2023-05-29 Fix warnings
2023-06-03 Fix catchup bug when resuming from idle
2023-06-03 Set the interface lights for idle and low power modes
2023-06-03 Fix moving pole
2023-06-03 Start fixing moving pole option 2
2023-06-03 Fix idle timeout
2023-06-04 Fix hue poles
2023-06-04 Migrate MovingPole to use std::array
2023-06-04 Migrate to std::array in effects
2023-06-04 Add test coverage for toggling Option2
    Also fix a divide-by-zero.
2023-06-04 Fix log format
2023-06-04 Remove redundant c-arrays
2023-06-04 Clean up EffectsTest
2023-06-04 Add test coverage for options
2023-06-07 Add a function to set the Teensy RTC
2023-07-26 Write out the pole lights in TeensyLightController.
2023-08-01 Remove outdated comment in InterfaceController.hpp
2023-08-19 Fix pole light output
2023-08-25 Add framework for building mini
2023-08-25 Flesh out mini.cpp
